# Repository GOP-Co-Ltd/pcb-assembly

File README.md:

# PCB Assembly

KiCad の基板データを読み込み、はんだペーストをパッドへ塗る装置の制御ソフトウェア。
Raspberry Pi 5 の上で Klipper にステージとディスペンサーを動かさせ、カメラで基板の位置を合わせ、ロードセルで高さを測ってから塗る。
操作はすべてブラウザから行う。

- 塗布: パッドごとの塗布設定、経路のプレビュー、位置合わせと高さ計測、初回パージの撮影確認、塗布
- 校正: カメラ、基準点、ノズル位置、ツールヘッドオフセット、吐出量、画像による塗布量の校正
- 基板: テスト塗布基板・格子基板・矩形基板の生成、PCB の情報の抽出
- 運用: LAN 上の複数機体の切替と操作権、通知音、設定履歴とバックアップ、WebUI からのソフトウェア更新

## 前提

- Raspberry Pi 5 と Raspberry Pi OS 64bit（Debian 13 trixie）
- Klipper の MCU、カメラ、ロードセルプローブ、オーガースクリュー式ディスペンサーを備えた機体。通知音を使うならスピーカー
- 機体とブラウザが同じ信頼できる LAN にあること（WebUI に認証は無い）

## クイックスタート

ホスト名を機体ごとに一意な名前へ変えた Raspberry Pi で、次の 3 行を実行する。

```sh
git clone https://github.com/GOP-Co-Ltd/pcb-assembly.git ~/pcb-assembly
cd ~/pcb-assembly && ./install.sh
sudo reboot
```

再起動したら、ブラウザで `http://<ホスト名>.local:8080` を開く。
途中で聞かれること（カメラやスピーカーの種類、機種）は [導入](docs/install.md) にある。

## 文書の地図

上から順に読めば、空の SD カードから日常の塗布と保守まで進める。

| 段階        | 文書                                                                                      | 内容                                                                 |
| ----------- | ----------------------------------------------------------------------------------------- | -------------------------------------------------------------------- |
| 1. 導入     | [導入](docs/install.md)                                                                   | 空の SD カードから WebUI が開くまで                                  |
| 2. 立ち上げ | [立ち上げ](docs/commissioning.md)                                                         | 新しい機体を塗布できる状態まで校正する順序と、各段の合格条件         |
| 3. 日常     | [日常の運用](docs/daily.md)                                                               | 塗布、ローディング、ノズル清掃、複数機体、通知音、データセットの収集 |
| 4. 保守     | [保守ガイド](docs/maintenance.md)                                                         | 更新、バックアップと復元、ロールバック、復旧、ホストの追加、ログ     |
| 確認        | [実機受け入れ試験](docs/acceptance.md)                                                    | 変更を merge する前に実機で確かめる項目と手順                        |
| 参照        | [設定キー一覧](docs/reference/config.md)                                                  | `machine.toml` に書けるキー                                          |
| 参照        | [ファイルと環境変数](docs/reference/files.md)                                             | 設定・データ・ログの置き場所と、起動時の環境変数                     |
| 開発        | [開発の手引き](docs/develop/index.md)                                                     | 不具合の報告、開発環境、検証、テストの書き方、実機なしでの画面確認   |
| 開発        | [アーキテクチャ](docs/develop/architecture.md)                                            | 層と依存方向、機能からコードへの地図、機能を足すときの変更先         |
| 設計        | [画像ベース吐出量キャリブレーション要件](docs/design/image-based-dispense-calibration.md) | 運転時の流量補正と、塗布量校正のデータ収集の要件                     |
| 設計        | [直径ベースの塗布量校正](docs/design/paste-volume-diameter-calibration.md)                | 塗布量の推定モデルと実測記録                                         |
| 設計        | [ピンセット式 PnP の運動制御](docs/design/pnp-tweezer-motion.md)                          | XYZ のファーム（Klipper の MCU に速度指令を足す案）、サーボ、RL      |
| 資産        | [マシン設定テンプレート](deploy/templates/README.md)                                      | 機種ごとの `machine.toml` と `printer.cfg` の初期値                  |
| 資産        | [GitHub Actions Runner](github-runner/README.md)                                          | CI 用の専用 Raspberry Pi                                             |

## ライセンス

既定は [MIT](LICENSE)。次のものは、それぞれのライセンスに従う。

| 対象                       | ライセンス                                        | 理由                                       |
| -------------------------- | ------------------------------------------------- | ------------------------------------------ |
| `src/firmware/pnp-motion/` | [GPLv3](src/firmware/pnp-motion/LICENSE)          | Klipper の MCU ファームを元にする          |
| `klipper/`                 | [GPLv3](klipper/LICENSE)                          | Klipper のコードから派生した Klippy の拡張 |
| `.claude/skills/yomiyasu/` | [MIT](.claude/skills/yomiyasu/LICENSE)（nanaism） | 外部から vendoring した skill              |

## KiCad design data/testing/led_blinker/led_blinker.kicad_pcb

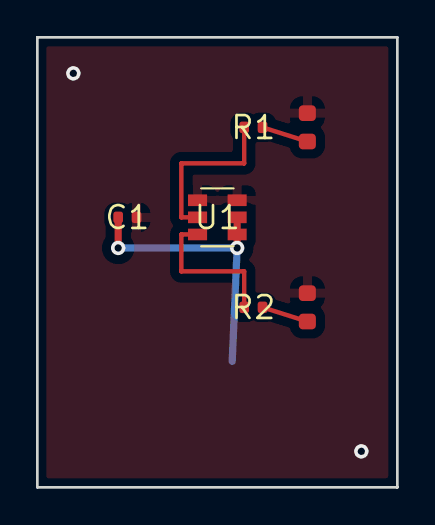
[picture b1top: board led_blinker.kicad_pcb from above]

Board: 2 copper layers, 20.0 x 25.0 mm, 7 parts (1 on the bottom side), 4 nets.

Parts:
C1: 100nF; C_0402_1005Metric
D1: LED_Red; LED_0603_1608Metric
D2: LED_Green; LED_0603_1608Metric
R1, R2: 330R; R_0402_1005Metric
R3: 10k; R_0603_1608Metric
U1: ATtiny85; SOT-23-6

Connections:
GND: C1.2, D1.2, D2.2, R3.2, U1.1, U1.6
LED1: D1.1, R1.1, R1.2, U1.2
LED2: D2.1, R2.1, R2.2, U1.3
VCC: C1.1, R3.1, U1.4, U1.5
